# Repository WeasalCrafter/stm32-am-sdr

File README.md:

<!-- kicad_template/README.md -->

# STM32-Based SDR Rated for 0.5MHz to 30MHz

This repository contains all KiCad files relating to my STM-32 SDR project.

The board is 4 layers, and 120mm by 60mm. The current version is v1.0, last finished 11/16/2026.

The idea of the project is to make an SDR that can demodulate RF from 0.5MHz to 30MHz, which includes AM broadcasts, some ameteur radio bands, and some digital broadcast signals. For the table I am going to have the project in a 3d printed case for the attendees to see, a poster/display board explaining the key points of it, and my laptop for showing the waterfall/spectrum graph received from it.

See renders from KiCad below.

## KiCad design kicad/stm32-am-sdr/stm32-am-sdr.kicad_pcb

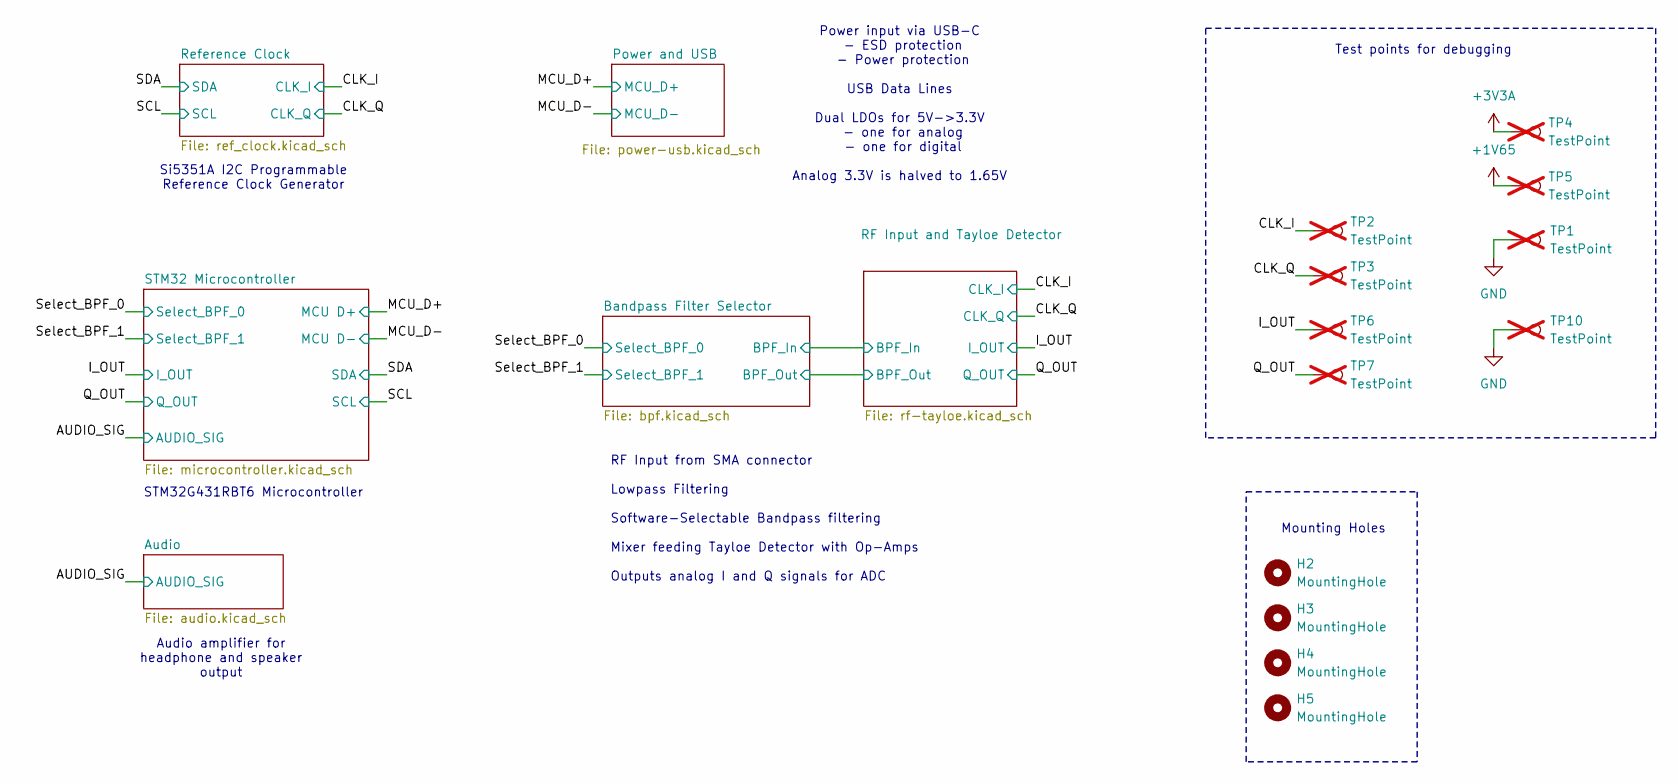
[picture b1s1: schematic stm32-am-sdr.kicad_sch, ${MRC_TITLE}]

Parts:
H2, H3, H4, H5: MountingHole; MountingHole_3.2mm_M3_Pad_TopBottom
TP1, TP2, TP3, TP4, TP5, TP6, TP7, TP10: TestPoint; TestPoint_Pad_D2.5mm; not fitted

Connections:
unnamed: TP1.1, TP10.1

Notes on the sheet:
Audio amplifier for headphone and speaker output
Power input via USB-C - ESD protection - Power protection USB Data Lines Dual LDOs for 5V->3.3V - one for analog - one for digital Analog 3.3V is halved to 1.65V
Test points for debugging
Si5351A I2C Programmable Reference Clock Generator
Mounting Holes
STM32G431RBT6 Microcontroller
RF Input from SMA connector Lowpass Filtering Software-Selectable Bandpass filtering Mixer feeding Tayloe Detector with Op-Amps Outputs analog I and Q signals for ADC

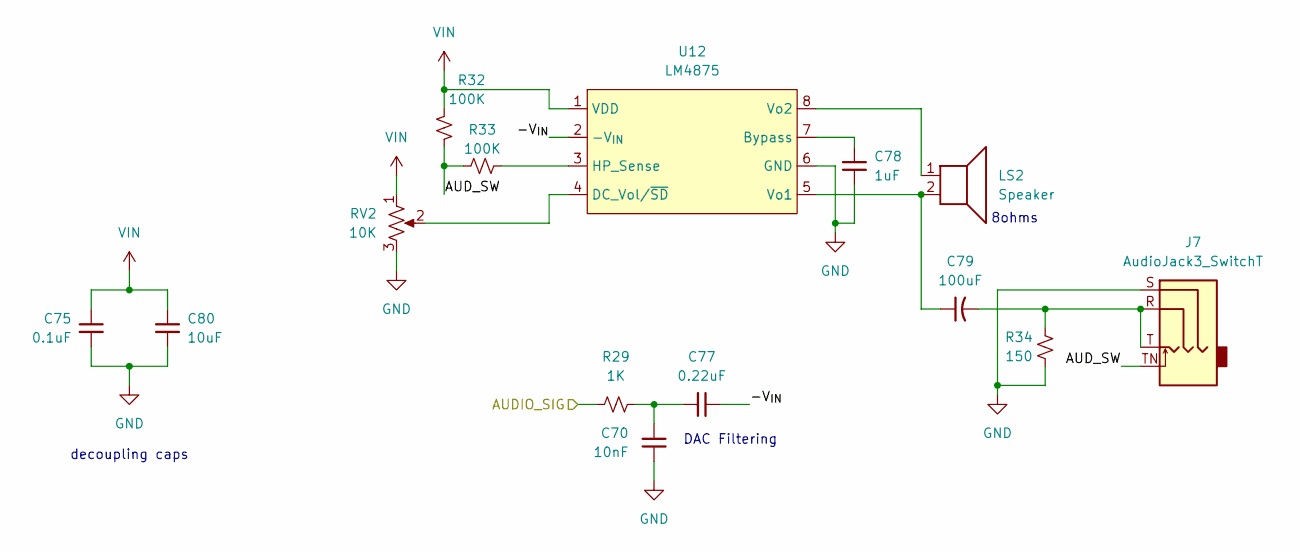
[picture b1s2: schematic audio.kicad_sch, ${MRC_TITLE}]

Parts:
C70: 10nF; C_0603_1608Metric; digikey_id 490-GCM1885C2A103GE02VCT-ND
C75: 0.1uF; C_0603_1608Metric; digikey_id 311-1779-1-ND
C77: 0.22uF; C_0603_1608Metric; digikey_id 13-CC0603JRX7R9BB224CT-ND
C78: 1uF; C_0603_1608Metric; digikey_id 311-3485-1-ND
C79: 100uF; CP_Elec_6.3x5.7; digikey_id 399-A768EB107M1ELAS036CT-ND
C80: 10uF; C_0805_2012Metric; digikey_id 13-CC0805KFX7R6BB106CT-ND
J7: AudioJack3_SwitchT; Jack_3.5mm_CUI_SJ-3524-SMT_Horizontal; digikey_id CP-3524SJTR-ND
LS2: Speaker; SolderWire-0.25sqmm_1x02_P4.2mm_D0.65mm_OD1.7mm
R29: 1K; R_0603_1608Metric; digikey_id 541-1.00KHCT-ND
R32, R33: 100K; R_0603_1608Metric; digikey_id 541-100KHCT-ND
R34: 150; R_0603_1608Metric; digikey_id RMCF0603FT150RCT-ND
RV2: 10K; RES-TH_RK10J12E0A0A; digikey_id 4809-RK10J11E0034-ND
U12: LM4875; JEITA_SOIC-8_3.9x4.9mm_P1.27mm; digikey_id 296-35282-2-ND

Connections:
/AUDIO_SIG: R29.1; also elsewhere on the board
/Audio/-V_{IN}: C77.2, U12.2 (-V_{IN})
/Audio/AUD_SW: J7.TN, R32.2, R33.1
GND: C70.2, C75.2, C78.2, C80.2, J7.S, R34.1, RV2.3, U12.6 (GND); also elsewhere on the board
unnamed: C70.1, C77.1, R29.2
unnamed: C79.2, J7.R, J7.T, R34.2
unnamed: C78.1, U12.7 (Bypass)
unnamed: RV2.2, U12.4 (DC_Vol/~SD)
unnamed: R33.2, U12.3 (HP_Sense)
unnamed: C79.1, LS2.2, U12.5 (Vo1)
unnamed: LS2.1, U12.8 (Vo2)
VIN: C75.1, C80.1, R32.1, RV2.1, U12.1 (VDD); also elsewhere on the board

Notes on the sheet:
8ohms
decoupling caps
DAC Filtering

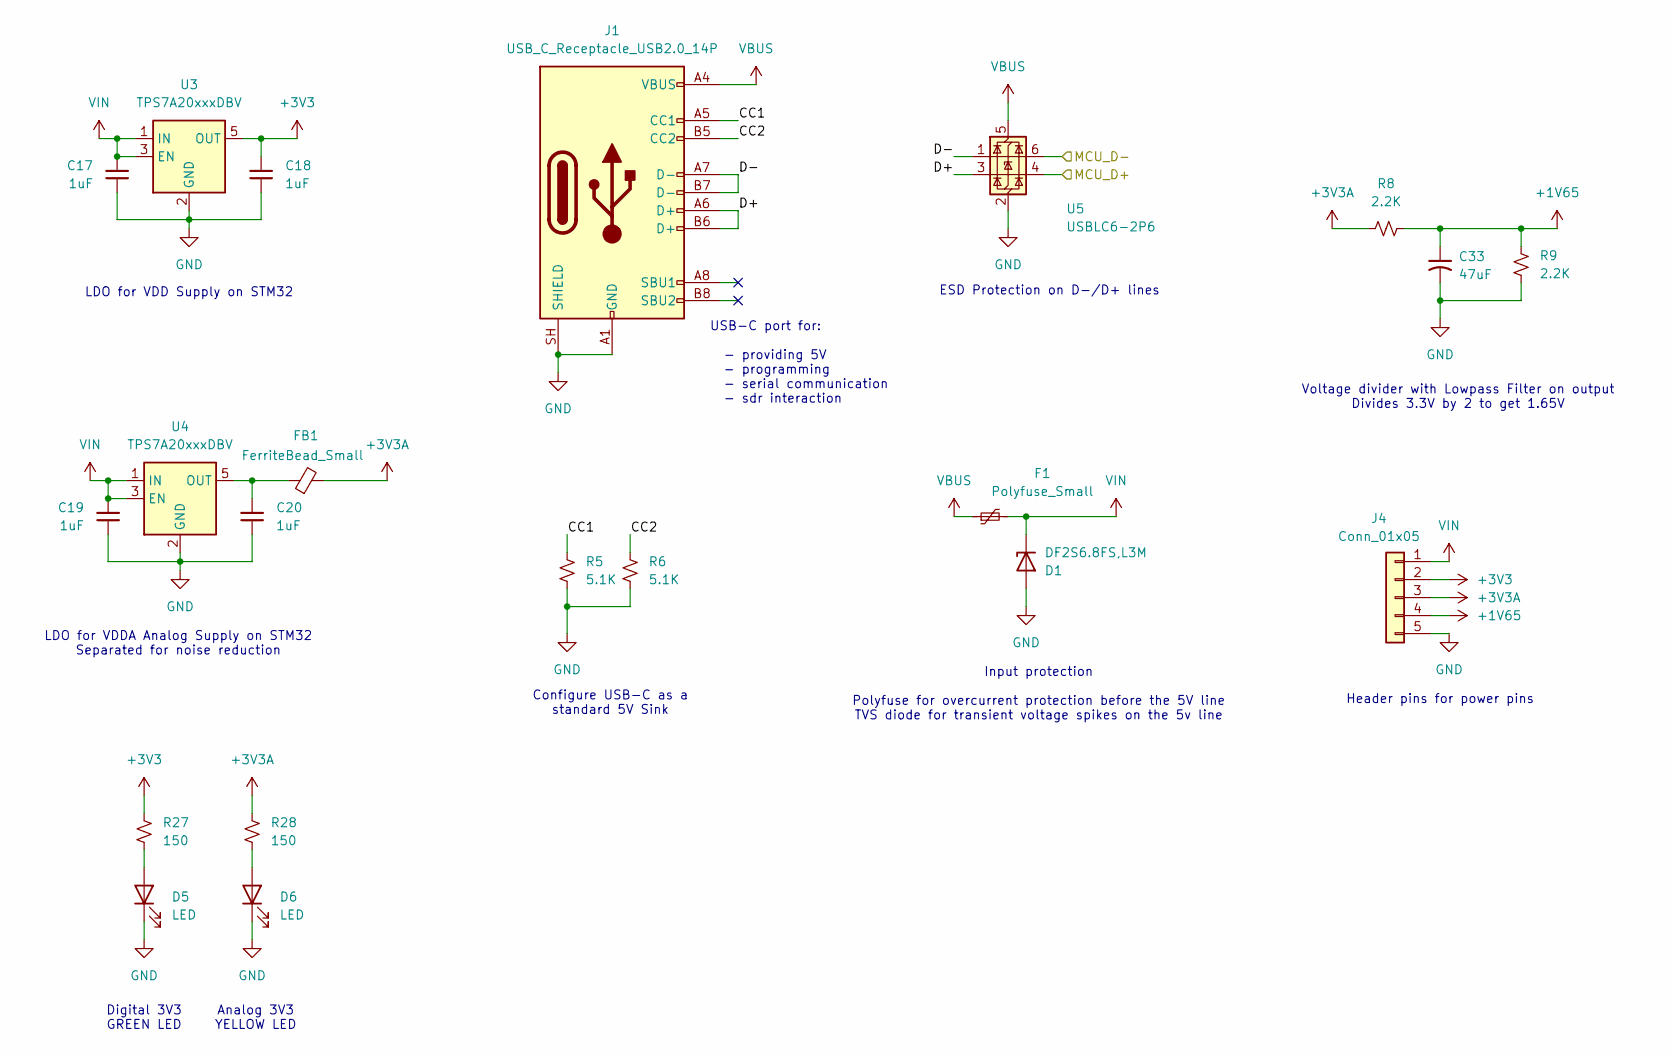
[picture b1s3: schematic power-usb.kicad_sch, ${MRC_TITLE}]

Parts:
C17, C18, C19, C20: 1uF; C_0603_1608Metric; digikey_id 311-3485-1-ND
C33: 47uF; C_1206_3216Metric; digikey_id 490-9673-1-ND
D1: DF2S6.8FS,L3M; D_SOD-923; digikey_id DF2S6.8FS(TL4D)TR-ND
D5: LED; LED_0603_1608Metric_Pad1.05x0.95mm_HandSolder; digikey_id 160-LTST-C190GKTTR-ND
D6: LED; LED_0603_1608Metric_Pad1.05x0.95mm_HandSolder; digikey_id 160-1184-2-ND
F1: Polyfuse_Small; Fuse_0805_2012Metric; digikey_id F2774TR-ND
FB1: FerriteBead_Small; L_0603_1608Metric; digikey_id 240-2378-2-ND
J1: USB_C_Receptacle_USB2.0_14P; USB_C_Receptacle_GCT_USB4105-xx-A_16P_TopMnt_Horizontal; digikey_id 2073-USB4105-GF-ATR-ND
J4: Conn_01x05; PinHeader_1x05_P2.54mm_Vertical
R5, R6: 5.1K; R_0603_1608Metric; digikey_id 311-5.10KHRCT-ND
R8, R9: 2.2K; R_0603_1608Metric; digikey_id A129692CT-ND
R27, R28: 150; R_0603_1608Metric; digikey_id RMCF0603FT150RCT-ND
U3, U4: TPS7A20xxxDBV; SOT-23-5; digikey_id 296-TPS7A2033PDBVRTR-ND
U5: USBLC6-2P6; SOT-666; digikey_id 497-5026-2-ND

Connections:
+1V65: C33.1, J4.4, R8.2, R9.2; also elsewhere on the board
+3V3: C18.1, J4.2, R27.1, U3.5 (OUT); also elsewhere on the board
+3V3A: FB1.2, J4.3, R8.1, R28.1; also elsewhere on the board
/MCU_D+: U5.4 (I/O2); also elsewhere on the board
/MCU_D-: U5.6 (I/O1); also elsewhere on the board
/Power and USB/CC1: J1.A5 (CC1), R5.2
/Power and USB/CC2: J1.B5 (CC2), R6.2
/Power and USB/D+: J1.A6 (D+), J1.B6 (D+), U5.3 (I/O2)
/Power and USB/D-: J1.A7 (D-), J1.B7 (D-), U5.1 (I/O1)
GND: C17.2, C18.2, C19.2, C20.2, C33.2, D1.2 (A), D5.1 (K), D6.1 (K), J1.A1 (GND), J1.A12 (GND), J1.B1 (GND), J1.B12 (GND), J1.SH (SHIELD), J4.5, R5.1, R6.1, R9.1, U3.2 (GND), U4.2 (GND), U5.2 (GND); also elsewhere on the board
unnamed: D5.2 (A), R27.2
unnamed: D6.2 (A), R28.2
unnamed: C20.1, FB1.1, U4.5 (OUT)
VBUS: F1.1, J1.A4 (VBUS), J1.A9 (VBUS), J1.B4 (VBUS), J1.B9 (VBUS), U5.5 (VBUS)
VIN: C17.1, C19.1, D1.1 (K), F1.2, J4.1, U3.1 (IN), U3.3 (EN), U4.1 (IN), U4.3 (EN); also elsewhere on the board

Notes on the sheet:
Voltage divider with Lowpass Filter on output Divides 3.3V by 2 to get 1.65V
LDO for VDD Supply on STM32
USB-C port for: - providing 5V - programming - serial communication - sdr interaction
Input protection Polyfuse for overcurrent protection before the 5V line TVS diode for transient voltage spikes on the 5v line
Digital 3V3 GREEN LED
Header pins for power pins
Analog 3V3 YELLOW LED
LDO for VDDA Analog Supply on STM32 Separated for noise reduction
Configure USB-C as a standard 5V Sink
ESD Protection on D-/D+ lines

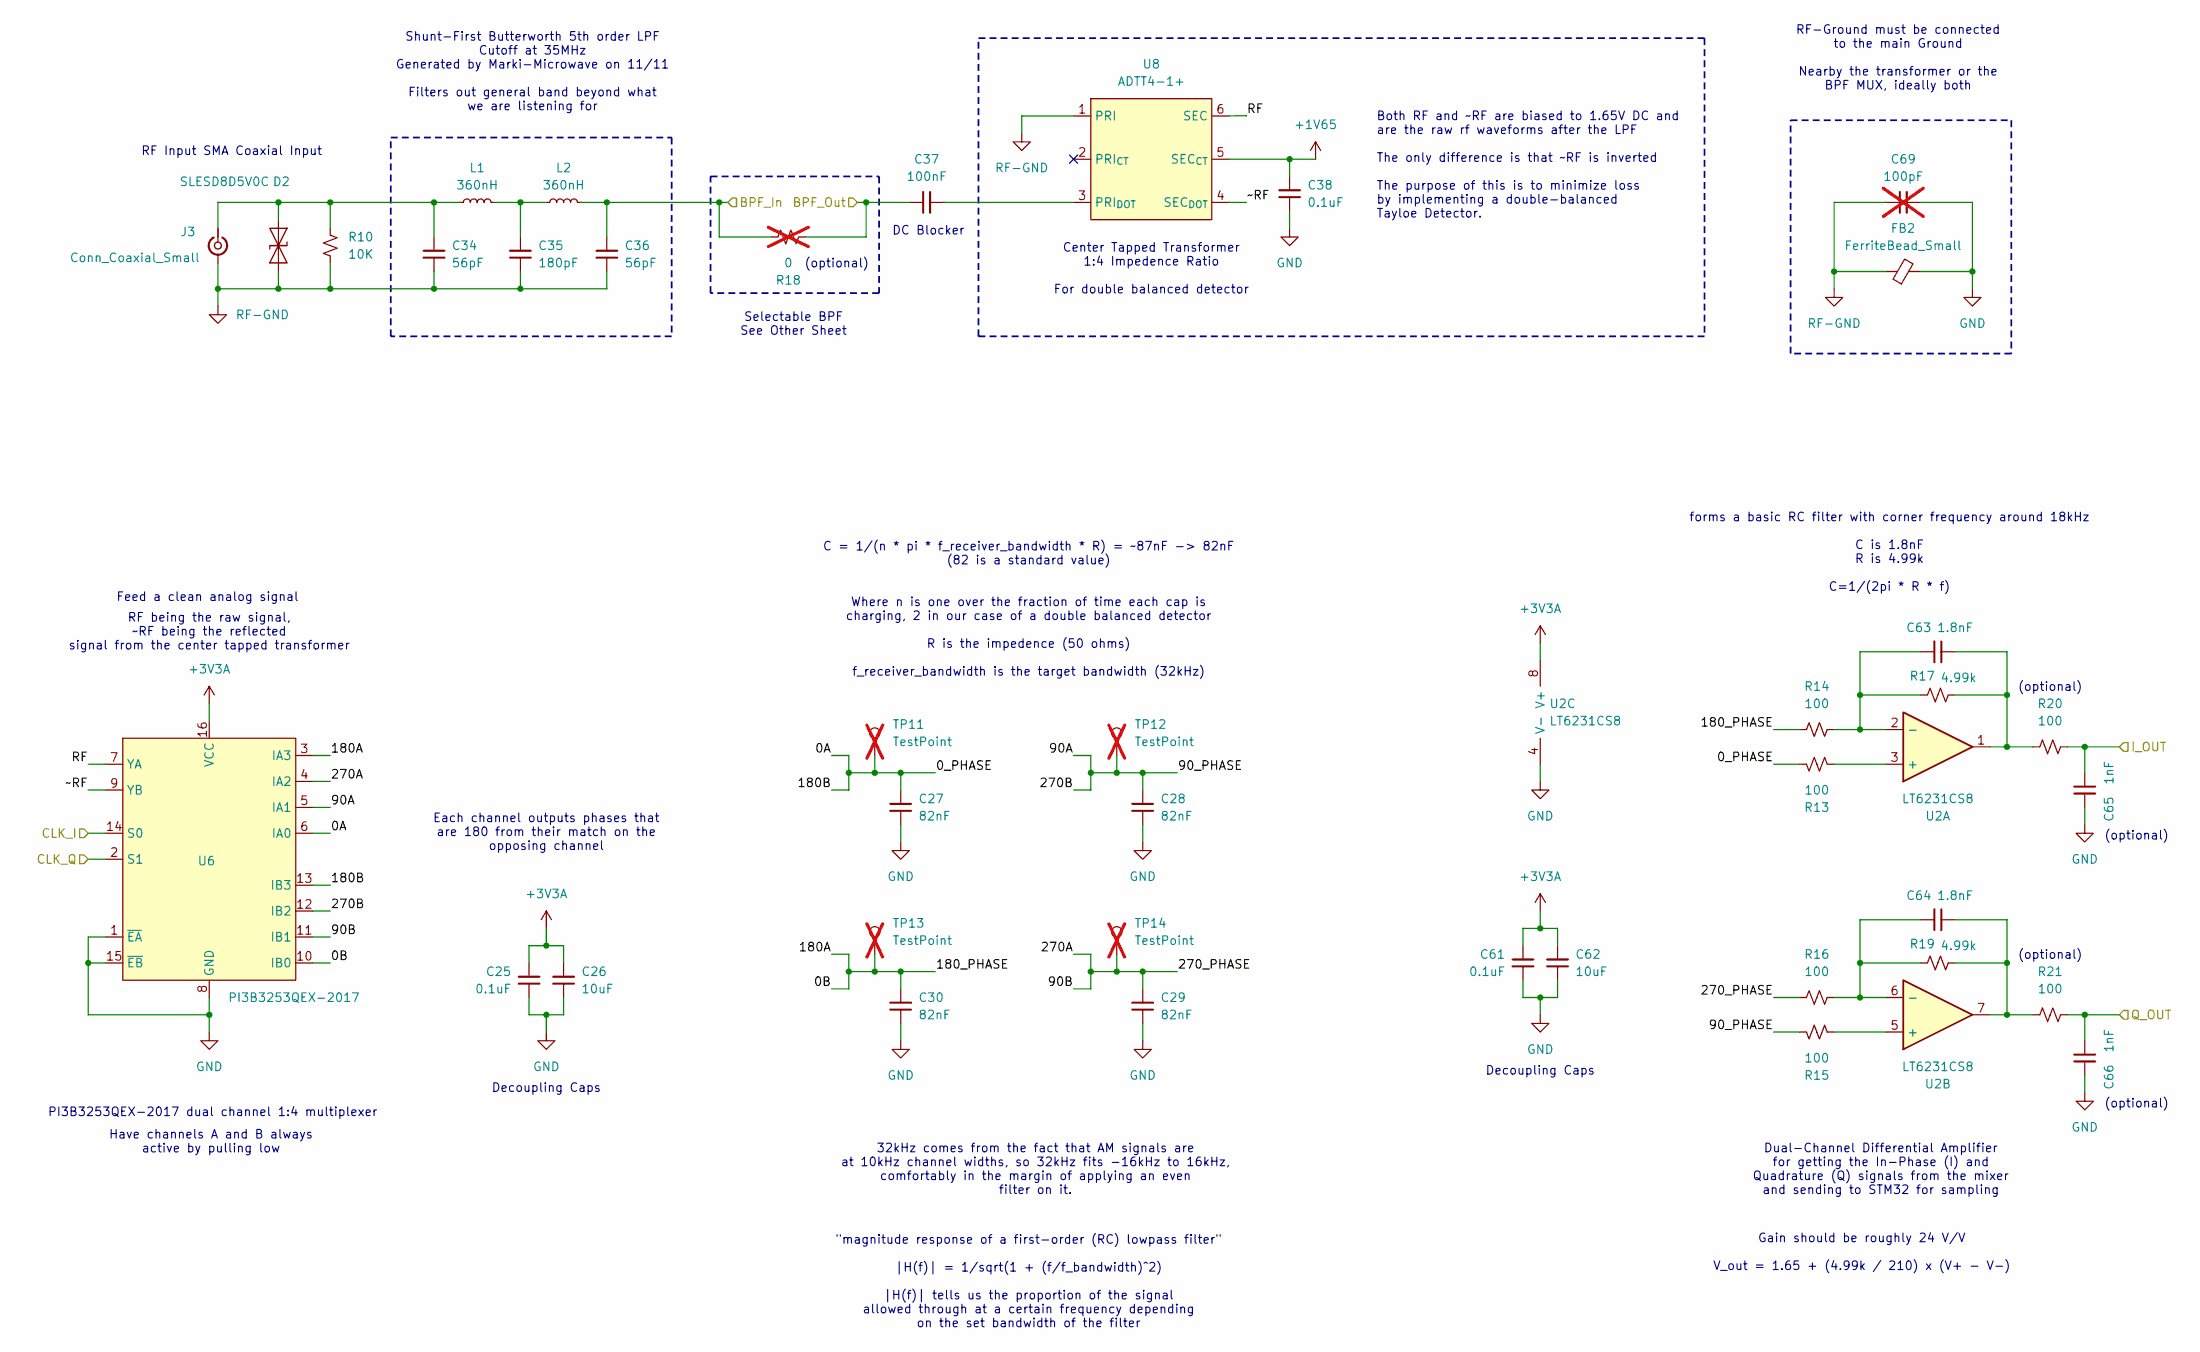
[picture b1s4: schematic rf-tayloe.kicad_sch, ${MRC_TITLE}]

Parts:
C25, C38, C61: 0.1uF; C_0603_1608Metric; digikey_id 311-1779-1-ND
C26, C62: 10uF; C_0805_2012Metric; digikey_id 13-CC0805KFX7R6BB106CT-ND
C27, C28, C29, C30: 82nF; C_1206_3216Metric; digikey_id 490-GRM3195C2A823GA01DCT-ND
C34, C36: 56pF; C_0603_1608Metric; digikey_id 311-3936-1-ND
C35: 180pF; C_0603_1608Metric; digikey_id 311-3923-1-ND
C37: 100nF; C_0603_1608Metric; digikey_id 311-1779-1-ND
C63, C64: 1.8nF; C_0603_1608Metric; digikey_id 490-GCM1885C1H182GA16DCT-ND
C65, C66: 1nF; C_0603_1608Metric; digikey_id 311-3916-1-ND
C69: 100pF; C_0603_1608Metric; digikey_id 311-3351-1-ND; not fitted
D2: SLESD8D5V0C; D_0402_1005Metric; digikey_id 5399-SLESD8D5V0CCT-ND
FB2: FerriteBead_Small; L_0603_1608Metric; digikey_id 240-2376-2-ND
J3: Conn_Coaxial_Small; SMA_Amphenol_132289_EdgeMount; digikey_id ACX1426-ND
L1, L2: 360nH; L_0805_2012Metric; digikey_id A129510CT-ND
R10: 10K; R_0603_1608Metric; digikey_id 541-10.0KHCT-ND
R13, R14, R15, R16, R20, R21: 100; R_0603_1608Metric; digikey_id RG16P100BCT-ND
R17, R19: 4.99k; R_0603_1608Metric; digikey_id RG16P4.99KBCT-ND
R18: 0; R_0603_1608Metric; digikey_id 4713-CAS06F0000CT-ND; not fitted
TP11, TP12, TP13, TP14: TestPoint; TestPoint_Pad_D2.5mm; not fitted
U2: LT6231CS8; JEITA_SOIC-8_3.9x4.9mm_P1.27mm; digikey_id LT6231CS8#TRPBFTR-ND
U6: PI3B3253QEX-2017; QSOP-16_3.9x4.9mm_P0.635mm; digikey_id 31-PI3B3253QEX-2017TR-ND
U8: ADTT4-1+; Mini-Circuits_CD636_H4.11mm; digikey_id 3157-ADTT4-1+TR-ND

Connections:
+1V65: C38.1, U8.5 (SEC_{CT}); also elsewhere on the board
+3V3A: C25.1, C26.1, C61.1, C62.1, U2.8 (V+), U6.16 (VCC); also elsewhere on the board
/Bandpass Filter Selector/BPF_In: C36.1, L2.2, R18.1; also elsewhere on the board
/Bandpass Filter Selector/BPF_Out: C37.1, R18.2; also elsewhere on the board
/CLK_I: U6.14 (S0); also elsewhere on the board
/CLK_Q: U6.2 (S1); also elsewhere on the board
/I_OUT: C65.2, R20.2; also elsewhere on the board
/Q_OUT: C66.2, R21.2; also elsewhere on the board
/RF Input and Tayloe Detector/0A: C27.1, R13.1, TP11.1, U6.6 (IA0), U6.13 (IB3); also elsewhere on the board
/RF Input and Tayloe Detector/0B: C30.1, R14.1, TP13.1, U6.3 (IA3), U6.10 (IB0); also elsewhere on the board
/RF Input and Tayloe Detector/270A: C29.1, R16.1, TP14.1, U6.4 (IA2), U6.11 (IB1); also elsewhere on the board
/RF Input and Tayloe Detector/270B: C28.1, R15.1, TP12.1, U6.5 (IA1), U6.12 (IB2); also elsewhere on the board
/RF Input and Tayloe Detector/RF: U6.7 (YA), U8.6 (SEC)
/RF Input and Tayloe Detector/~RF: U6.9 (YB), U8.4 (SEC_{DOT})
GND: C25.2, C26.2, C27.2, C28.2, C29.2, C30.2, C38.2, C61.2, C62.2, C65.1, C66.1, C69.2, FB2.2, U2.4 (V-), U6.1 (~EA), U6.8 (GND), U6.15 (~EB); also elsewhere on the board
unnamed: C35.1, L1.2, L2.1
unnamed: C63.2, R17.2, R20.1, U2.1
unnamed: C64.2, R19.2, R21.1, U2.7
unnamed: C34.1, D2.2 (A2), J3.1 (In), L1.1, R10.1
unnamed: R13.2, U2.3 (+)
unnamed: C63.1, R14.2, R17.1, U2.2 (-)
unnamed: R15.2, U2.5 (+)
unnamed: C64.1, R16.2, R19.1, U2.6 (-)
unnamed: C37.2, U8.3 (PRI_{DOT})
RF-GND: C34.2, C35.2, C36.2, C69.1, D2.1 (A1), FB2.1, J3.2 (Ext), R10.2, U8.1 (PRI); also elsewhere on the board

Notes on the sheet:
C = 1/(n * pi * f_receiver_bandwidth * R) = ~87nF -> 82nF (82 is a standard value) Where n is one over the fraction of time each cap is charging, 2 in our case of a double balanced detector R is the impedence (50 ohms) f_receiver_bandwidth is the target bandwidth (32kHz)
32kHz comes from the fact that AM signals are at 10kHz channel widths, so 32kHz fits -16kHz to 16kHz, comfortably in the margin of applying an even filter on it.
Have channels A and B always active by pulling low
Decoupling Caps
Both RF and ~RF are biased to 1.65V DC and are the raw rf waveforms after the LPF The only difference is that ~RF is inverted The purpose of this is to minimize loss by implementing a double-balanced Tayloe Detector.
(optional)
Gain should be roughly 24 V/V V_out = 1.65 + (4.99k / 210) x (V+ - V-)
Dual-Channel Differential Amplifier for getting the In-Phase (I) and Quadrature (Q) signals from the mixer and sending to STM32 for sampling
forms a basic RC filter with corner frequency around 18kHz C is 1.8nF R is 4.99k C=1/(2pi * R * f)
PI3B3253QEX-2017 dual channel 1:4 multiplexer
"magnitude response of a first-order (RC) lowpass filter" |H(f)| = 1/sqrt(1 + (f/f_bandwidth)^2) |H(f)| tells us the proportion of the signal allowed through at a certain frequency depending on the set bandwidth of the filter
DC Blocker
Selectable BPF See Other Sheet
Center Tapped Transformer 1:4 Impedence Ratio For double balanced detector
Each channel outputs phases that are 180 from their match on the opposing channel
RF being the raw signal, ~RF being the reflected signal from the center tapped transformer
RF Input SMA Coaxial Input
Feed a clean analog signal
RF-Ground must be connected to the main Ground Nearby the transformer or the BPF MUX, ideally both
Shunt-First Butterworth 5th order LPF Cutoff at 35MHz Generated by Marki-Microwave on 11/11 Filters out general band beyond what we are listening for

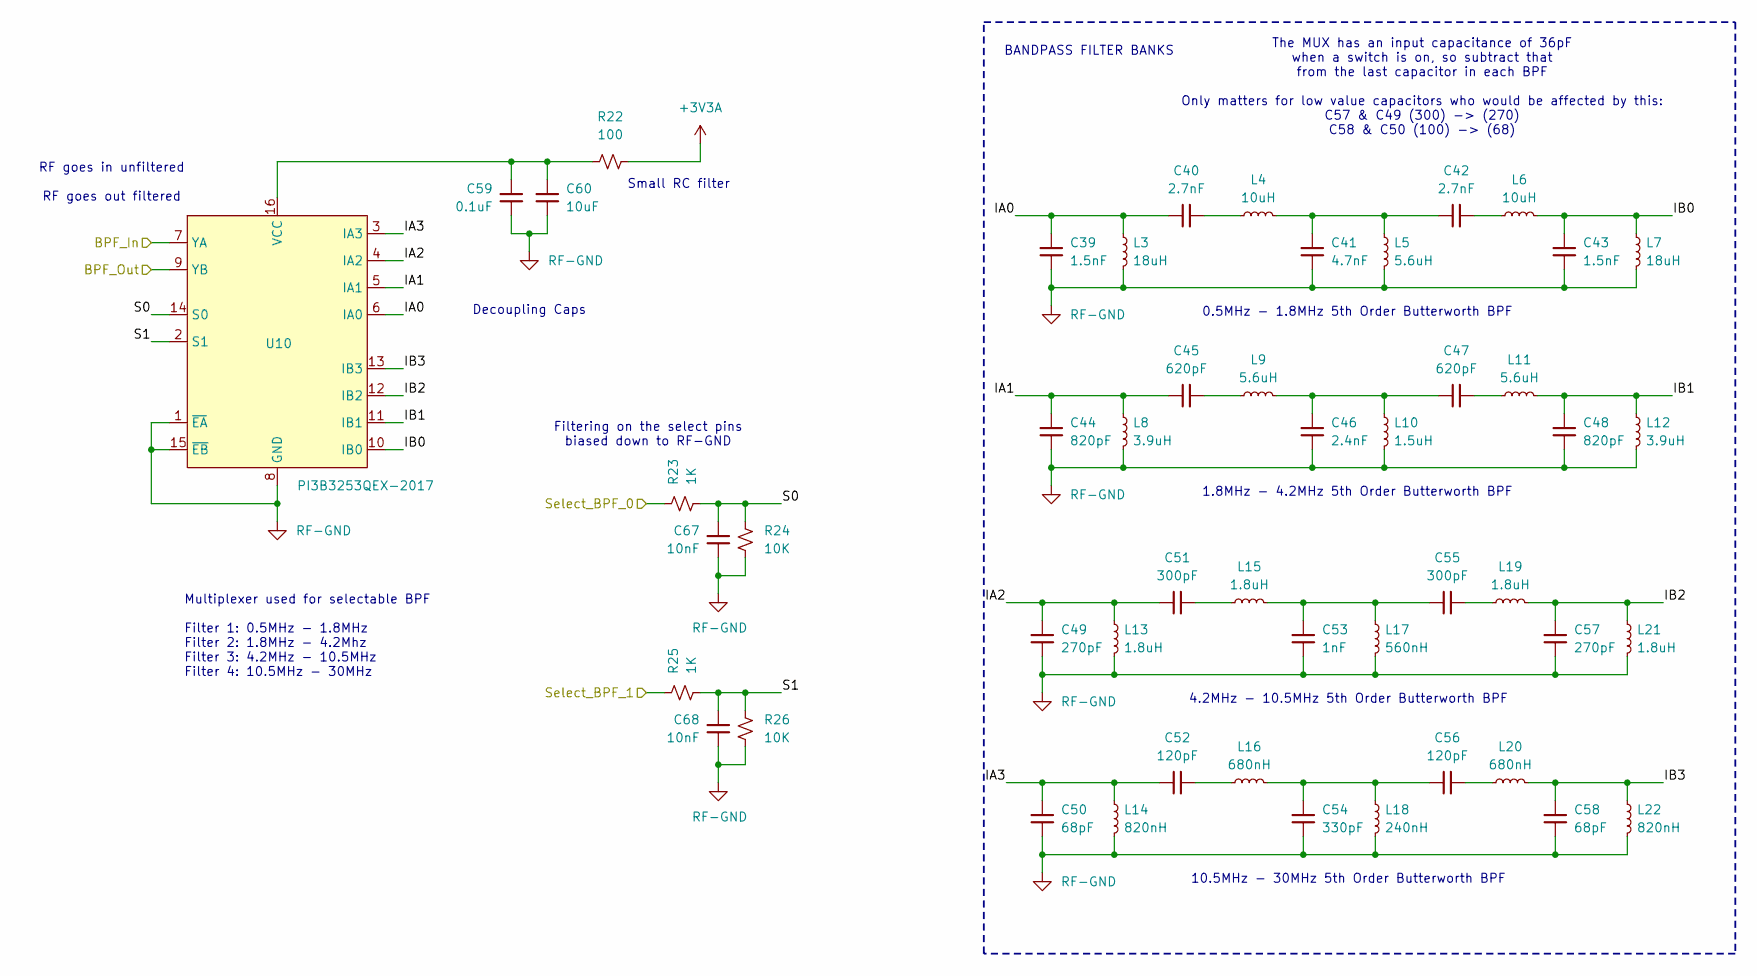
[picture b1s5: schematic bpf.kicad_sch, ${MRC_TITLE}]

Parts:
C39, C43: 1.5nF; C_0603_1608Metric; digikey_id 13-CC0603GRNPO9BN152CT-ND
C40, C42: 2.7nF; C_0603_1608Metric; digikey_id 13-CC0603GRNPO9BN272CT-ND
C41: 4.7nF; C_0603_1608Metric; digikey_id 490-GCM1885C1H472GA16DCT-ND
C44, C48: 820pF; C_0603_1608Metric; digikey_id 311-3941-1-ND
C45, C47: 620pF; C_0603_1608Metric; digikey_id 13-CC0603GRNPO9BN621CT-ND
C46: 2.4nF; C_0603_1608Metric; digikey_id 490-GCM1885C1H242GA16DCT-ND
C49, C57: 270pF; C_0603_1608Metric; digikey_id 311-3930-1-ND
C50, C58: 68pF; C_0603_1608Metric; digikey_id 311-3938-1-ND
C51, C55: 300pF; C_0603_1608Metric; digikey_id 13-CC0603GRNPO9BN301CT-ND
C52, C56: 120pF; C_0603_1608Metric; digikey_id 311-3918-1-ND
C53: 1nF; C_0603_1608Metric; digikey_id 311-3916-1-ND
C54: 330pF; C_0603_1608Metric; digikey_id 311-3353-1-ND
C59: 0.1uF; C_0603_1608Metric; digikey_id 311-1779-1-ND
C60: 10uF; C_0805_2012Metric; digikey_id 13-CC0805KFX7R6BB106CT-ND
C67, C68: 10nF; C_0603_1608Metric; digikey_id 311-1085-1-ND
L3, L7: 18uH; L_Murata_LQH2MCNxxxx02_2.0x1.6mm; digikey_id 490-8391-1-ND
L4, L6: 10uH; L_1008_2520Metric; digikey_id 490-LQH2HPN100MGRLCT-ND
L5, L9, L11: 5.6uH; L_Coilcraft_0805HQ_2012Metric; digikey_id 587-LSQMB201616T5R6JCT-ND
L8, L12: 3.9uH; L_1008_2520Metric; digikey_id 490-5713-1-ND
L10: 1.5uH; L_1210_3225Metric; digikey_id 587-2425-1-ND
L13, L15, L19, L21: 1.8uH; L_Coilcraft_0805HQ_2012Metric; digikey_id 587-LSQMB201616T1R8JCT-ND
L14, L22: 820nH; L_1008_2520Metric; digikey_id 490-5704-1-ND
L16, L20: 680nH; L_1008_2520Metric; digikey_id 490-5702-1-ND
L17: 560nH; L_1008_2520Metric; digikey_id 490-5700-1-ND
L18: 240nH; L_0805_2012Metric; digikey_id 490-LQW2BASR24G00LCT-ND
R22: 100; R_0603_1608Metric; digikey_id RG16P100BCT-ND
R23, R25: 1K; R_0603_1608Metric; digikey_id 541-1.00KHCT-ND
R24, R26: 10K; R_0603_1608Metric; digikey_id 541-10.0KHCT-ND
U10: PI3B3253QEX-2017; QSOP-16_3.9x4.9mm_P0.635mm; digikey_id 31-PI3B3253QEX-2017TR-ND

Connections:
+3V3A: R22.2; also elsewhere on the board
/Bandpass Filter Selector/BPF_In: U10.7 (YA); also elsewhere on the board
/Bandpass Filter Selector/BPF_Out: U10.9 (YB); also elsewhere on the board
/Bandpass Filter Selector/IA0: C39.1, C40.1, L3.1, U10.6 (IA0)
/Bandpass Filter Selector/IA1: C44.1, C45.1, L8.1, U10.5 (IA1)
/Bandpass Filter Selector/IA2: C49.1, C51.1, L13.1, U10.4 (IA2)
/Bandpass Filter Selector/IA3: C50.1, C52.1, L14.1, U10.3 (IA3)
/Bandpass Filter Selector/IB0: C43.1, L6.2, L7.1, U10.10 (IB0)
/Bandpass Filter Selector/IB1: C48.1, L11.2, L12.1, U10.11 (IB1)
/Bandpass Filter Selector/IB2: C57.1, L19.2, L21.1, U10.12 (IB2)
/Bandpass Filter Selector/IB3: C58.1, L20.2, L22.1, U10.13 (IB3)
/Bandpass Filter Selector/S0: C67.1, R23.2, R24.1, U10.14 (S0)
/Bandpass Filter Selector/S1: C68.1, R25.2, R26.1, U10.2 (S1)
/Select_BPF_0: R23.1; also elsewhere on the board
/Select_BPF_1: R25.1; also elsewhere on the board
unnamed: C40.2, L4.1
unnamed: C41.1, C42.1, L4.2, L5.1
unnamed: C42.2, L6.1
unnamed: C45.2, L9.1
unnamed: C46.1, C47.1, L9.2, L10.1
unnamed: C47.2, L11.1
unnamed: C51.2, L15.1
unnamed: C52.2, L16.1
unnamed: C53.1, C55.1, L15.2, L17.1
unnamed: C54.1, C56.1, L16.2, L18.1
unnamed: C55.2, L19.1
unnamed: C56.2, L20.1
unnamed: C59.1, C60.1, R22.1, U10.16 (VCC)
RF-GND: C39.2, C41.2, C43.2, C44.2, C46.2, C48.2, C49.2, C50.2, C53.2, C54.2, C57.2, C58.2, C59.2, C60.2, C67.2, C68.2, L3.2, L5.2, L7.2, L8.2, L10.2, L12.2, L13.2, L14.2, L17.2, L18.2, L21.2, L22.2, R24.2, R26.2, U10.1 (~EA), U10.8 (GND), U10.15 (~EB); also elsewhere on the board

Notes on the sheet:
0.5MHz - 1.8MHz 5th Order Butterworth BPF
4.2MHz - 10.5MHz 5th Order Butterworth BPF
Filtering on the select pins biased down to RF-GND
10.5MHz - 30MHz 5th Order Butterworth BPF
RF goes in unfiltered RF goes out filtered
1.8MHz - 4.2MHz 5th Order Butterworth BPF
The MUX has an input capacitance of 36pF when a switch is on, so subtract that from the last capacitor in each BPF Only matters for low value capacitors who would be affected by this: C57 & C49 (300) -> (270) C58 & C50 (100) -> (68)
Small RC filter
Decoupling Caps
BANDPASS FILTER BANKS
Multiplexer used for selectable BPF Filter 1: 0.5MHz - 1.8MHz Filter 2: 1.8MHz - 4.2Mhz Filter 3: 4.2MHz - 10.5MHz Filter 4: 10.5MHz - 30MHz

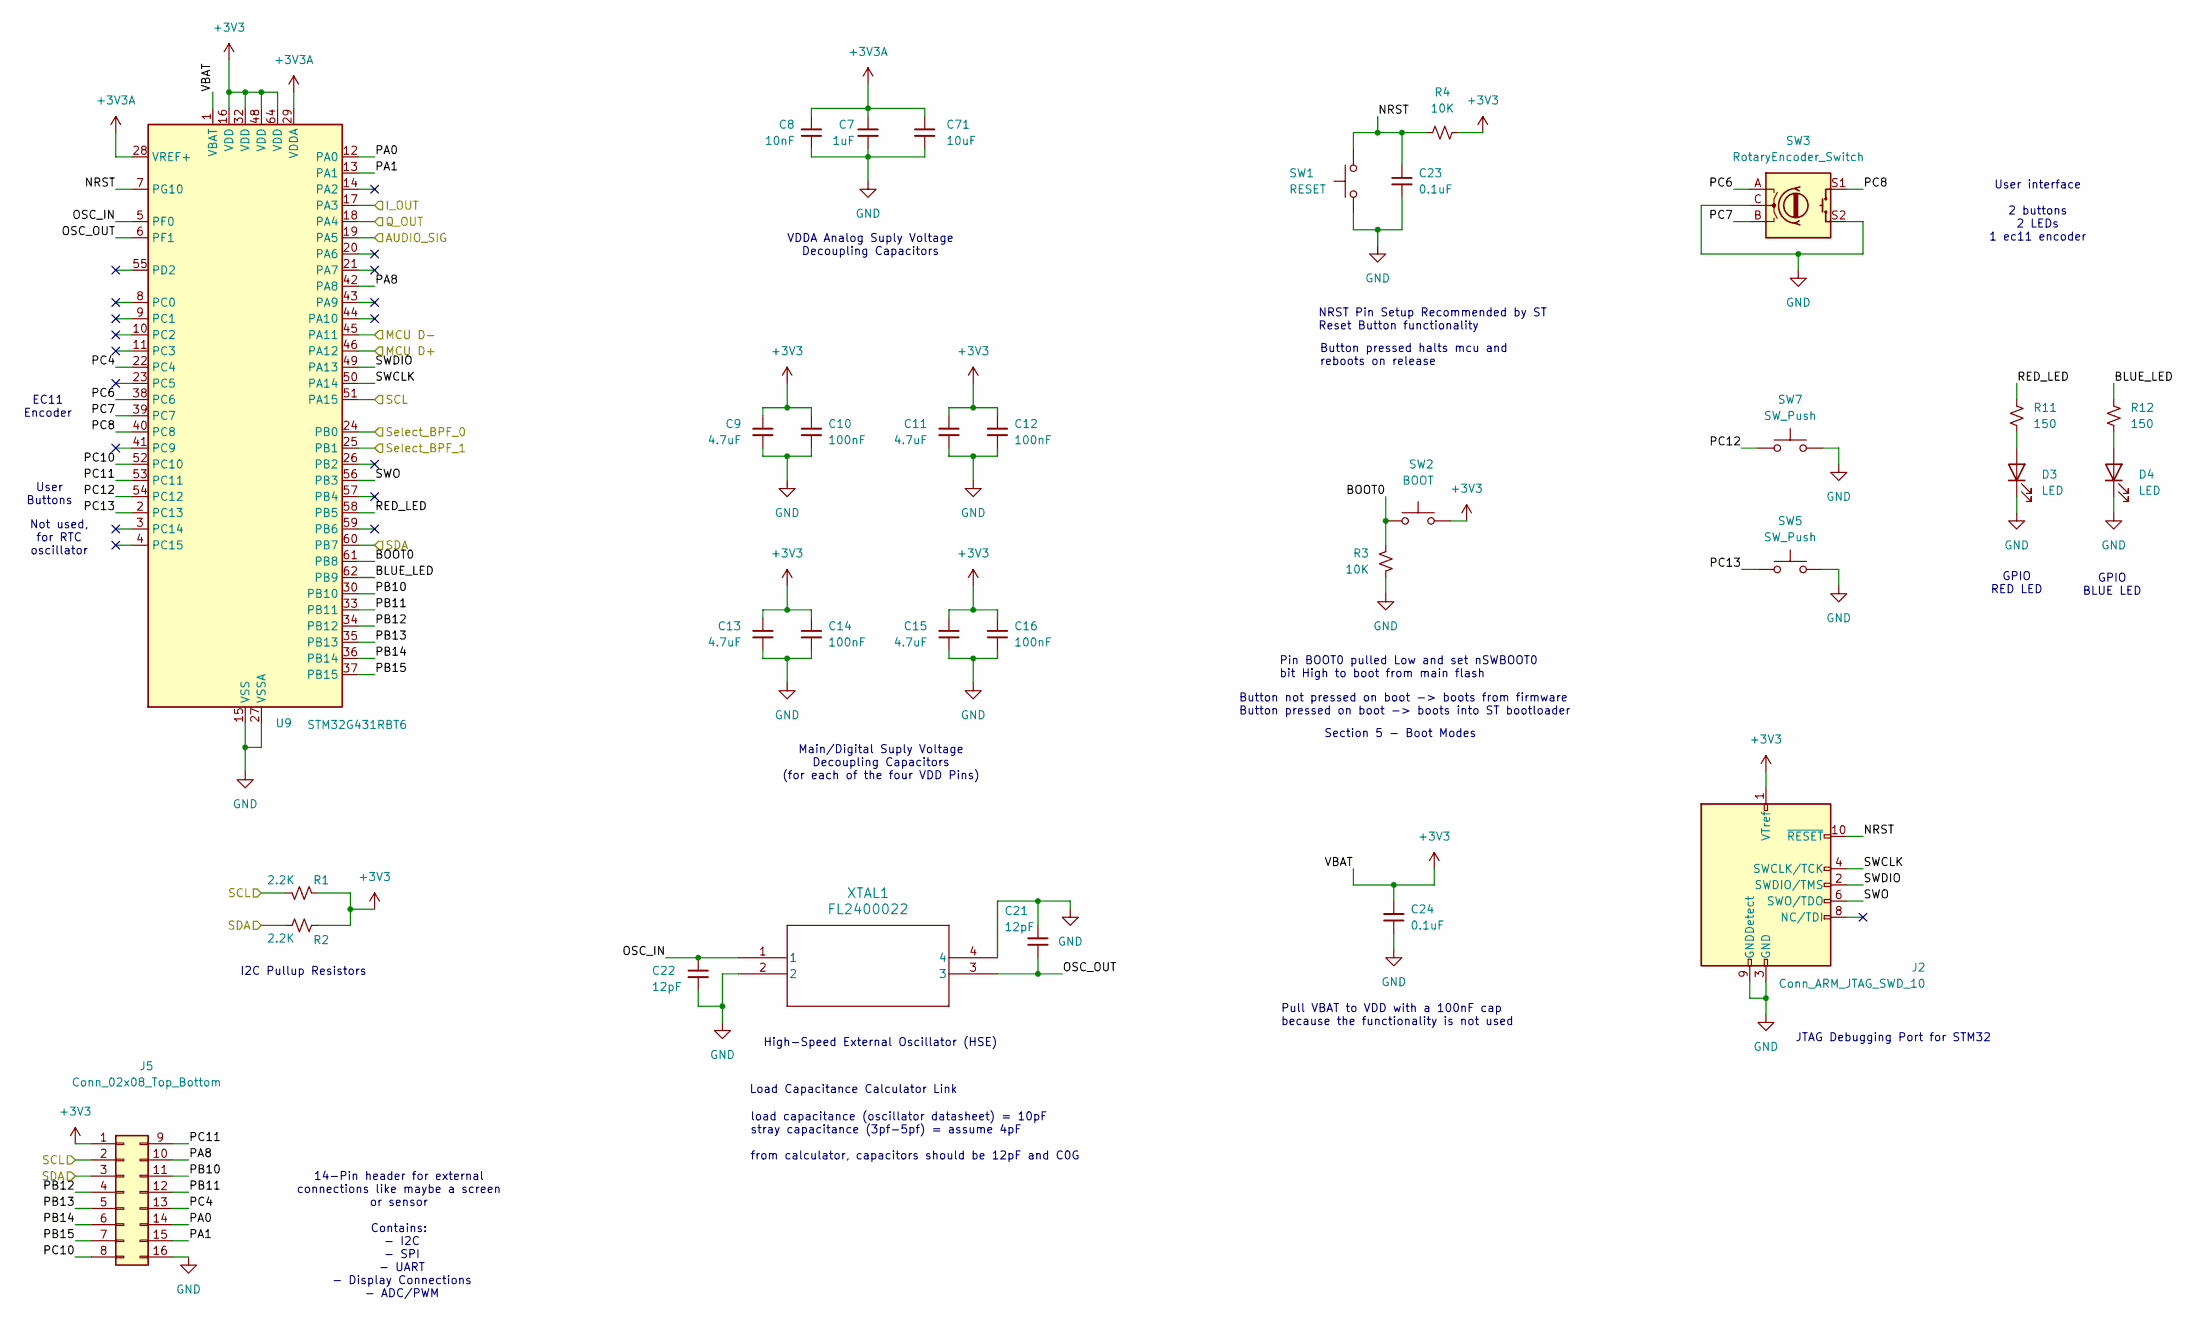
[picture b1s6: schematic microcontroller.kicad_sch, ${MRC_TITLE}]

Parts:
C7: 1uF; C_0603_1608Metric; digikey_id 311-3485-1-ND
C8: 10nF; C_0603_1608Metric; digikey_id 311-1085-1-ND
C9, C11, C13, C15: 4.7uF; C_0603_1608Metric; digikey_id 311-1785-1-ND
C10, C12, C14, C16: 100nF; C_0603_1608Metric; digikey_id 311-1779-1-ND
C21, C22: 12pF; C_0603_1608Metric; digikey_id 311-3917-1-ND
C23, C24: 0.1uF; C_0603_1608Metric; digikey_id 311-1779-1-ND
C71: 10uF; C_0805_2012Metric; digikey_id 13-CC0805KFX7R6BB106CT-ND
D3: LED; LED_0603_1608Metric_Pad1.05x0.95mm_HandSolder; digikey_id 160-1436-2-ND
D4: LED; LED_0603_1608Metric_Pad1.05x0.95mm_HandSolder; digikey_id 160-1827-2-ND
J2: Conn_ARM_JTAG_SWD_10; PinHeader_2x05_P2.54mm_Vertical
J5: Conn_02x08_Top_Bottom; PinHeader_2x08_P2.54mm_Vertical
R1, R2: 2.2K; R_0603_1608Metric; digikey_id A129692CT-ND
R3, R4: 10K; R_0603_1608Metric; digikey_id 541-10.0KHCT-ND
R11, R12: 150; R_0603_1608Metric; digikey_id RMCF0603FT150RCT-ND
SW1: RESET; SW_PUSH_6mm_H4.3mm; digikey_id SW400-ND
SW2: BOOT; SW_PUSH_6mm_H4.3mm; digikey_id SW400-ND
SW3: RotaryEncoder_Switch; RotaryEncoder_Alps_EC11E-Switch_Vertical_H20mm; digikey_id 4809-EC11E15244B2-ND
SW5, SW7: SW_Push; SW_PUSH-12mm; digikey_id SW411-ND
U9: STM32G431RBT6; LQFP-64_10x10mm_P0.5mm; digikey_id 497-19471-ND
XTAL1: FL2400022; Crystal_SMD_3225-4Pin_3.2x2.5mm; digikey_id FL2400022TR-ND

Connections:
+3V3: C9.1, C10.1, C11.1, C12.1, C13.1, C14.1, C15.1, C16.1, C24.1, J2.1 (VTref), J5.1, R1.1, R2.2, R4.2, SW2.1, U9.1 (VBAT), U9.16 (VDD), U9.32 (VDD), U9.48 (VDD), U9.64 (VDD); also elsewhere on the board
+3V3A: C7.1, C8.1, C71.1, U9.28 (VREF+), U9.29 (VDDA); also elsewhere on the board
/AUDIO_SIG: U9.19 (PA5); also elsewhere on the board
/I_OUT: U9.17 (PA3); also elsewhere on the board
/MCU_D+: U9.46 (PA12); also elsewhere on the board
/MCU_D-: U9.45 (PA11); also elsewhere on the board
/Q_OUT: U9.18 (PA4); also elsewhere on the board
/SCL: J5.2, R1.2, U9.51 (PA15); also elsewhere on the board
/SDA: J5.3, R2.1, U9.60 (PB7); also elsewhere on the board
/STM32 Microcontroller/BLUE_LED: R12.1, U9.62 (PB9)
/STM32 Microcontroller/BOOT0: R3.1, SW2.2, U9.61 (PB8); also elsewhere on the board
/STM32 Microcontroller/NRST: C23.1, J2.10 (~RESET), R4.1, SW1.2, U9.7 (PG10); also elsewhere on the board
/STM32 Microcontroller/OSC_IN: C22.1, U9.5 (PF0), XTAL1.1
/STM32 Microcontroller/OSC_OUT: C21.2, U9.6 (PF1), XTAL1.3
/STM32 Microcontroller/PA0: J5.14, U9.12 (PA0)
/STM32 Microcontroller/PA1: J5.15, U9.13 (PA1)
/STM32 Microcontroller/PA8: J5.10, U9.42 (PA8)
/STM32 Microcontroller/PB10: J5.11, U9.30 (PB10)
/STM32 Microcontroller/PB11: J5.12, U9.33 (PB11)
/STM32 Microcontroller/PB12: J5.4, U9.34 (PB12)
/STM32 Microcontroller/PB13: J5.5, U9.35 (PB13)
/STM32 Microcontroller/PB14: J5.6, U9.36 (PB14)
/STM32 Microcontroller/PB15: J5.7, U9.37 (PB15)
/STM32 Microcontroller/PC4: J5.13, U9.22 (PC4)
/STM32 Microcontroller/PC6: SW3.A, U9.38 (PC6)
/STM32 Microcontroller/PC7: SW3.B, U9.39 (PC7)
/STM32 Microcontroller/PC8: SW3.S1, U9.40 (PC8)
/STM32 Microcontroller/PC10: J5.8, U9.52 (PC10)
/STM32 Microcontroller/PC11: J5.9, U9.53 (PC11)
/STM32 Microcontroller/PC12: SW7.1, U9.54 (PC12); also elsewhere on the board
/STM32 Microcontroller/PC13: SW5.1, U9.2 (PC13); also elsewhere on the board
/STM32 Microcontroller/RED_LED: R11.1, U9.58 (PB5)
/STM32 Microcontroller/SWCLK: J2.4 (SWCLK/TCK), U9.50 (PA14)
/STM32 Microcontroller/SWDIO: J2.2 (SWDIO/TMS), U9.49 (PA13)
/STM32 Microcontroller/SWO: J2.6 (SWO/TDO), U9.56 (PB3)
/Select_BPF_0: U9.24 (PB0); also elsewhere on the board
/Select_BPF_1: U9.25 (PB1); also elsewhere on the board
GND: C7.2, C8.2, C9.2, C10.2, C11.2, C12.2, C13.2, C14.2, C15.2, C16.2, C21.1, C22.2, C23.2, C24.2, C71.2, D3.1 (K), D4.1 (K), J2.3 (GND), J2.5 (GND), J2.9 (GNDDetect), J5.16, R3.2, SW1.1, SW3.C, SW3.S2, SW5.2, SW7.2, U9.15 (VSS), U9.27 (VSSA), U9.31 (VSS), U9.47 (VSS), U9.63 (VSS), XTAL1.2, XTAL1.4; also elsewhere on the board
unnamed: D3.2 (A), R11.2
unnamed: D4.2 (A), R12.2

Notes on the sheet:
NRST Pin Setup Recommended by ST Reset Button functionality
Button not pressed on boot -> boots from firmware Button pressed on boot -> boots into ST bootloader
I2C Pullup Resistors
Section 5 - Boot Modes
14-Pin header for external connections like maybe a screen or sensor Contains: - I2C - SPI - UART - Display Connections - ADC/PWM
Load Capacitance Calculator Link
Button pressed halts mcu and reboots on release
High-Speed External Oscillator (HSE)
Main/Digital Suply Voltage Decoupling Capacitors (for each of the four VDD Pins)
load capacitance (oscillator datasheet) = 10pF stray capacitance (3pf-5pf) = assume 4pF from calculator, capacitors should be 12pF and C0G
Pin BOOT0 pulled Low and set nSWBOOT0 bit High to boot from main flash
EC11 Encoder
VDDA Analog Suply Voltage Decoupling Capacitors
User interface 2 buttons 2 LEDs 1 ec11 encoder
Pull VBAT to VDD with a 100nF cap because the functionality is not used
Not used, for RTC oscillator
GPIO BLUE LED
JTAG Debugging Port for STM32
User Buttons
GPIO RED LED
